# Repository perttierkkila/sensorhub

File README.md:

sensorhub
=========

Arduino-based sensor-board with wireless link

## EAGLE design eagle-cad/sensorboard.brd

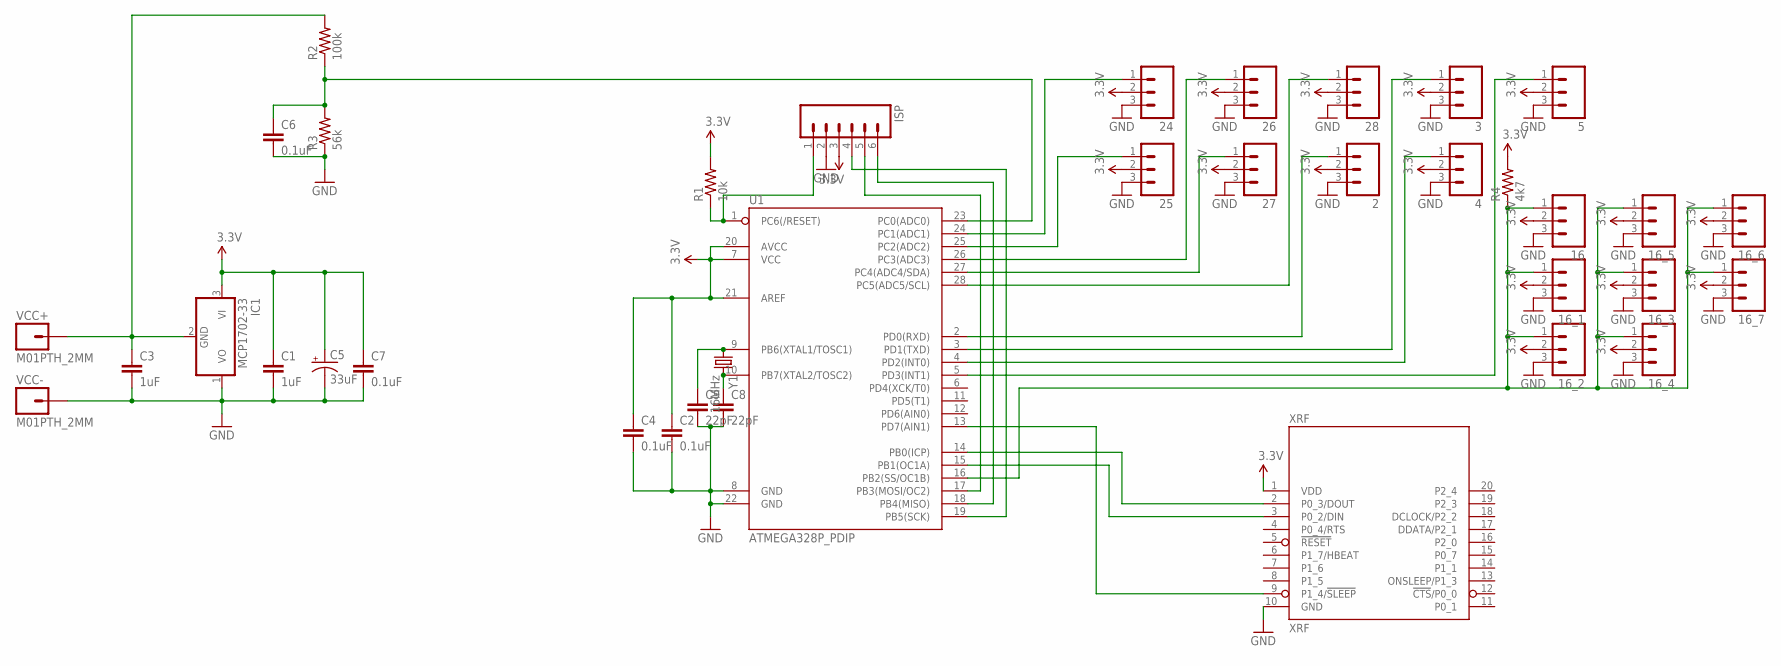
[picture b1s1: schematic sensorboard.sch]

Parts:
2, 3, 4, 5, 16, 16_1, 16_2, 16_3, 16_4, 16_5, 16_6, 16_7, 24, 25, 26, 27, 28: M031X03_NO_SILK; 1X03_NO_SILK
C1, C3: 1uF; CAP-PTH-SMALLEZ
C2, C4, C6, C7: 0.1uF; CAP-PTH-SMALLEZ
C5: 33uF; CPOL-RADIAL-10UF-25V
C8, C9: 22pF; CAP-PTH-SMALLEZ
IC1: MCP1702-33; TO92
ISP: M06SIP; 1X06
R1: 10k; AXIAL-0.3EZ
R2: 100k; AXIAL-0.3EZ
R3: 56k; AXIAL-0.3EZ
R4: 4k7; AXIAL-0.3EZ
U1: ATMEGA328P_PDIP; DIL28-3
VCC+: M01PTH_2MM; 1X01_2MM
VCC-: M01PTH_2MM; 1X01_2MM
XRF: XRF
Y1: 16MHz; HC49US

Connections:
3.3V: 2.2, 3.2, 4.2, 5.2, 16.2, 16_1.2, 16_2.2, 16_3.2, 16_4.2, 16_5.2, 16_6.2, 16_7.2, 24.2, 25.2, 26.2, 27.2, 28.2, C1.1, C2.1, C4.1, C5.1 (+), C7.1, IC1.3 (VI), ISP.3, R1.P$2 (2), R4.P$2 (2), U1.7 (VCC), U1.20 (AVCC), U1.21 (AREF), XRF.1 (VDD)
GND: 2.3, 3.3, 4.3, 5.3, 16.3, 16_1.3, 16_2.3, 16_3.3, 16_4.3, 16_5.3, 16_6.3, 16_7.3, 24.3, 25.3, 26.3, 27.3, 28.3, C1.2, C2.2, C3.2, C4.2, C5.2 (-), C6.2, C7.2, C8.2, C9.2, IC1.1 (VO), ISP.2, R3.P$1 (1), U1.8 (GND), U1.22 (GND), VCC-.1, XRF.10 (GND)
unnamed: ISP.1, R1.P$1 (1), U1.1 (PC6(/RESET))
unnamed: 28.1, U1.28 (PC5(ADC5/SCL))
unnamed: ISP.6, U1.18 (PB4(MISO))
unnamed: ISP.4, U1.19 (PB5(SCK))
unnamed: ISP.5, U1.17 (PB3(MOSI/OC2))
unnamed: 2.1, U1.2 (PD0(RXD))
unnamed: C3.1, IC1.2 (GND), R2.P$2 (2), VCC+.1
unnamed: 24.1, U1.24 (PC1(ADC1))
unnamed: U1.15 (PB1(OC1A)), XRF.3 (P0_2/DIN)
unnamed: U1.13 (PD7(AIN1)), XRF.9 (P1_4/!SLEEP)
unnamed: 3.1, U1.3 (PD1(TXD))
unnamed: 5.1, U1.5 (PD3(INT1))
unnamed: 4.1, U1.4 (PD2(INT0))
unnamed: C9.1, U1.9 (PB6(XTAL1/TOSC1)), Y1.1
unnamed: 16.1, 16_1.1, 16_2.1, 16_3.1, 16_4.1, 16_5.1, 16_6.1, 16_7.1, R4.P$1 (1), U1.16 (PB2(SS/OC1B))
unnamed: C8.1, U1.10 (PB7(XTAL2/TOSC2)), Y1.2
unnamed: U1.14 (PB0(ICP)), XRF.2 (P0_3/DOUT)
unnamed: 25.1, U1.25 (PC2(ADC2))
unnamed: C6.1, R2.P$1 (1), R3.P$2 (2), U1.23 (PC0(ADC0))
unnamed: 26.1, U1.26 (PC3(ADC3))
unnamed: 27.1, U1.27 (PC4(ADC4/SDA))

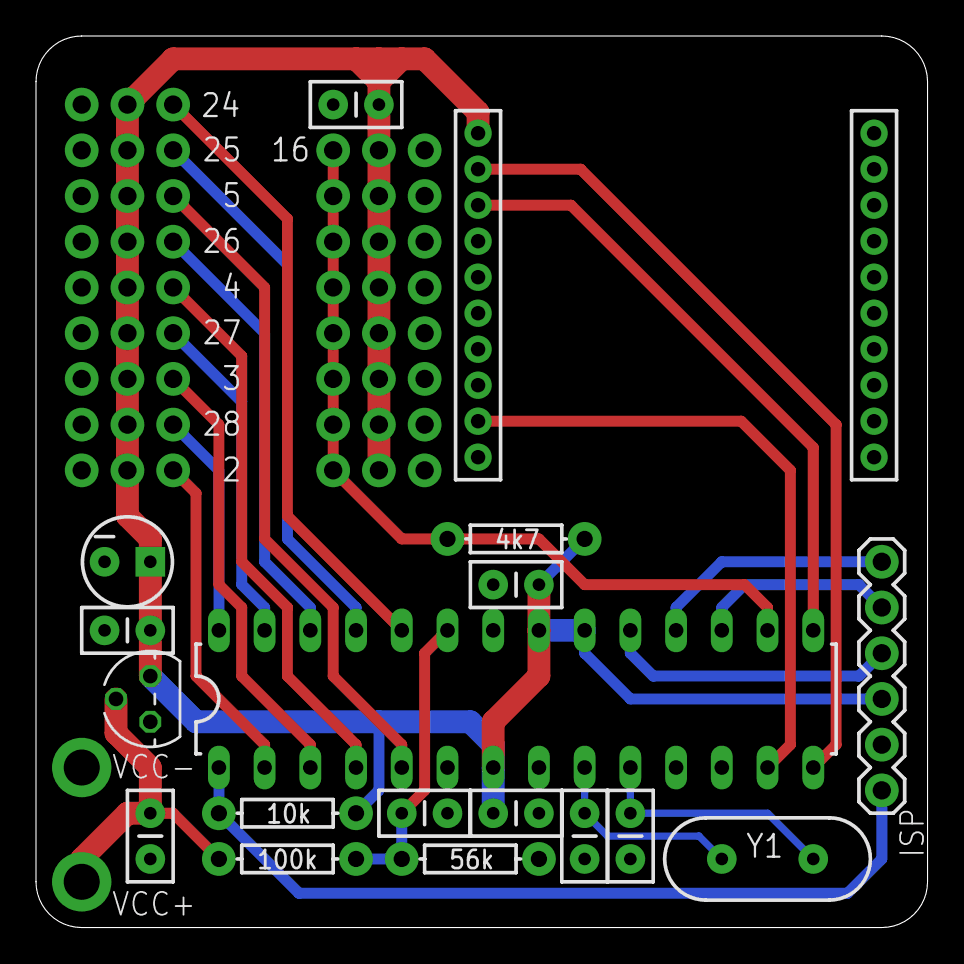
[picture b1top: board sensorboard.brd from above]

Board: 2 copper layers, 49.5 x 49.5 mm, 37 parts (0 on the bottom side), 23 nets.

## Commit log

2013-04-02 Added Eagle schema + board
2013-09-14 Fixed crystal cap values
2013-09-14 Fixed resistor divider cap value

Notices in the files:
parts and their libraries:
SparkFun-Connectors: Licensing: CC v3.0 Share-Alike You are welcome to use this library for commercial purposes.
